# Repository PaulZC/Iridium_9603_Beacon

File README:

########################
# Iridium 9603N Beacon #
########################

A lightweight Iridium 9603N + GPS Beacon (Tracker)
Suitable for High Altitude Ballooning

*** Version 3 now includes u-blox SAM-M8Q GNSS and the option of solar power ***
You can find the latest (untested) files in:
https://github.com/PaulZC/Iridium_9603_Beacon/tree/master/V3
Details for the tested breadboard prototype can be found in:
https://github.com/PaulZC/Iridium_9603N_Solar_Beacon

The current stable release is Version 2:

See Iridium_9603_Beacon.pdf for a description of the project:
https://github.com/PaulZC/Iridium_9603_Beacon/blob/master/Iridium_9603_Beacon.pdf

See Iridium_9603_Beacon_V2.pdf for the PCB schematics, overlays and BOM:
https://github.com/PaulZC/Iridium_9603_Beacon/blob/master/Iridium_9603_Beacon_V2.pdf

The Arduino code can be found in Arduino\Iridium9603Beacon:
https://github.com/PaulZC/Iridium_9603_Beacon/tree/master/Arduino/Iridium9603Beacon

The Eagle files can be found in Eagle\V2:
https://github.com/PaulZC/Iridium_9603_Beacon/tree/master/Eagle/V2

This project is distributed under a Creative Commons Attribution + Share-alike (BY-SA) licence.
Please refer to section 5 of the licence for the Disclaimer of Warranties and Limitation of Liability.

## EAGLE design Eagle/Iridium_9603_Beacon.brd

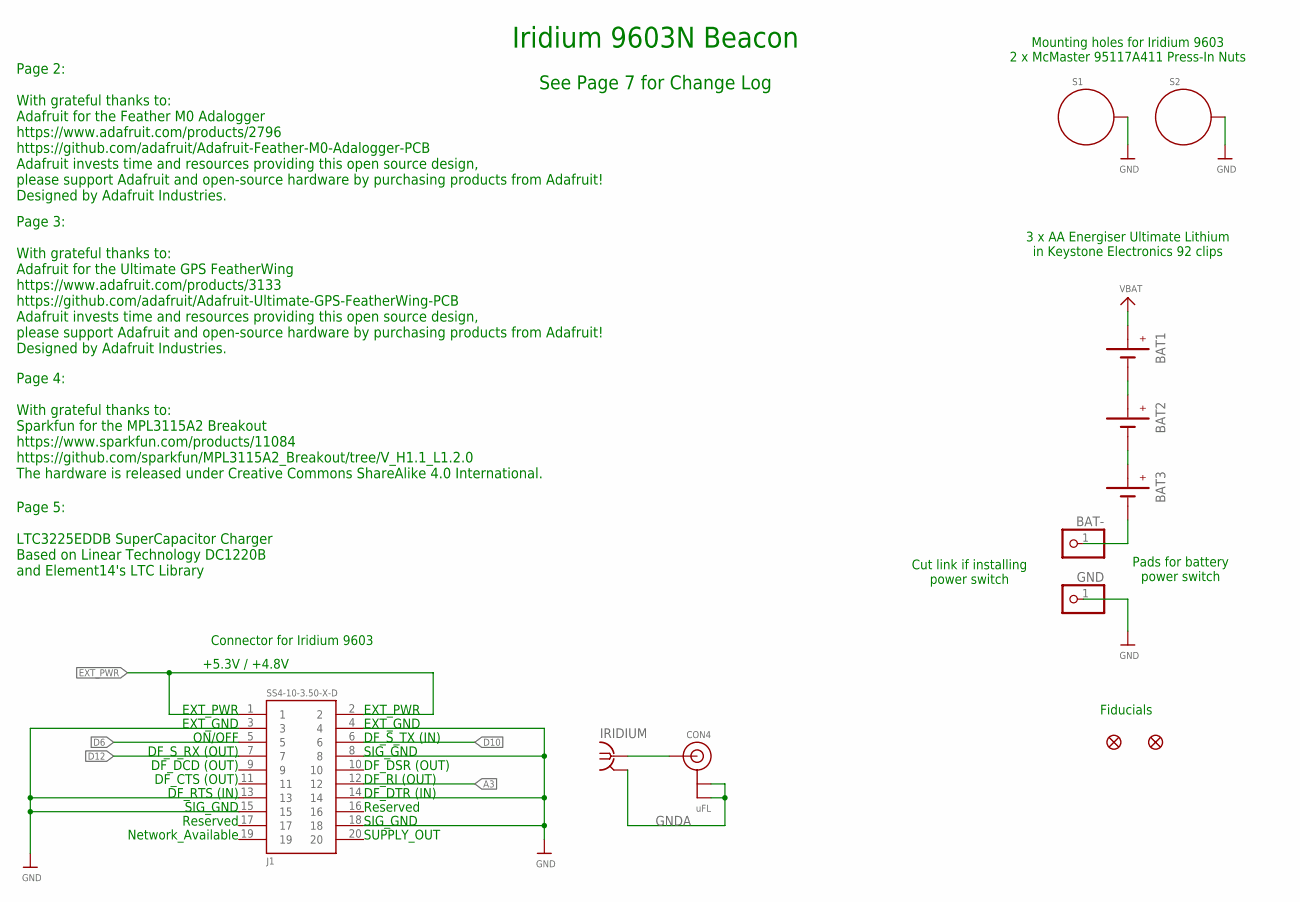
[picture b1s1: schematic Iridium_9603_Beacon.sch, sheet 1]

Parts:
BAT1, BAT2, BAT3: BATTERYKEYSTONE92; BATTERY-AAA-KEYSTONE92
BAT-: PINHD-1X1; 1X01
CON4: uFL; U.FL
FD1, FD2: FIDUCIAL1X2; FIDUCIAL-1X2
GND: PINHD-1X1; 1X01
IRIDIUM: SMA-142-0711-821/826; J502-ND-142-0711-821/826
J1: SS4-10-3.50-X-D
S1, S2: STANDOFF_ELECTRICALMCMASTER-95117A411; STANDOFF-ELECTRICAL-MCMASTER-95117A411

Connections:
A3: J1.12; also elsewhere on the board
D6: J1.5; also elsewhere on the board
D10: J1.6; also elsewhere on the board
D12: J1.7; also elsewhere on the board
EXT_PWR: J1.1, J1.2; also elsewhere on the board
GND: GND.1, J1.3, J1.4, J1.8, J1.13, J1.14, J1.15, J1.18, S1.P1, S2.P1; also elsewhere on the board
GNDA: CON4.1 (GND), CON4.2 (GND), IRIDIUM.G@1 (2), IRIDIUM.G@2 (2), IRIDIUM.G@3 (2), IRIDIUM.G@4 (2)
unnamed: CON4.3 (SIGNAL), IRIDIUM.1
unnamed: BAT1.GND@1 (-), BAT1.GND@2 (-), BAT2.PWR@1 (+), BAT2.PWR@2 (+)
unnamed: BAT3.GND@1 (-), BAT3.GND@2 (-), BAT-.1
unnamed: BAT2.GND@1 (-), BAT2.GND@2 (-), BAT3.PWR@1 (+), BAT3.PWR@2 (+)
VBAT: BAT1.PWR@1 (+), BAT1.PWR@2 (+); also elsewhere on the board

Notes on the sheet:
3 x AA Energiser Ultimate Lithium in Keystone Electronics 92 clips
Connector for Iridium 9603
Mounting holes for Iridium 9603 2 x McMaster 95117A411 Press-In Nuts
Iridium 9603N Beacon
Page 2: With grateful thanks to: Adafruit for the Feather M0 Adalogger https://www.adafruit.com/products/2796 https://github.com/adafruit/Adafruit-Feather-M0-Adalogger-PCB Adafruit invests time and resources providing this open source design, please support Adafruit and open-source hardware by purc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
Page 3: With grateful thanks to: Adafruit for the Ultimate GPS FeatherWing https://www.adafruit.com/products/3133 https://github.com/adafruit/Adafruit-Ultimate-GPS-FeatherWing-PCB Adafruit invests time and resources providing this open source design, please support Adafruit and open-source hardware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
Page 4: With grateful thanks to: Sparkfun for the MPL3115A2 Breakout https://www.sparkfun.com/products/11084 https://github.com/sparkfun/MPL3115A2_Breakout/tree/V_H1.1_L1.2.0 The hardware is released under Creative Commons ShareAlike 4.0 International.
EXT_PWR
EXT_GND
ON/OFF
DF_S_RX (OUT)
DF_DCD (OUT)
DF_CTS (OUT)
DF_RTS (IN)
SIG_GND
Reserved
Network_Available
DF_S_TX (IN)
DF_DSR (OUT)
DF_RI (OUT)
DF_DTR (IN)
SUPPLY_OUT
Page 5: LTC3225EDDB SuperCapacitor Charger Based on Linear Technology DC1220B and Element14's LTC Library
+5.3V / +4.8V
Fiducials
See Page 7 for Change Log
Pads for battery power switch
Cut link if installing power switch

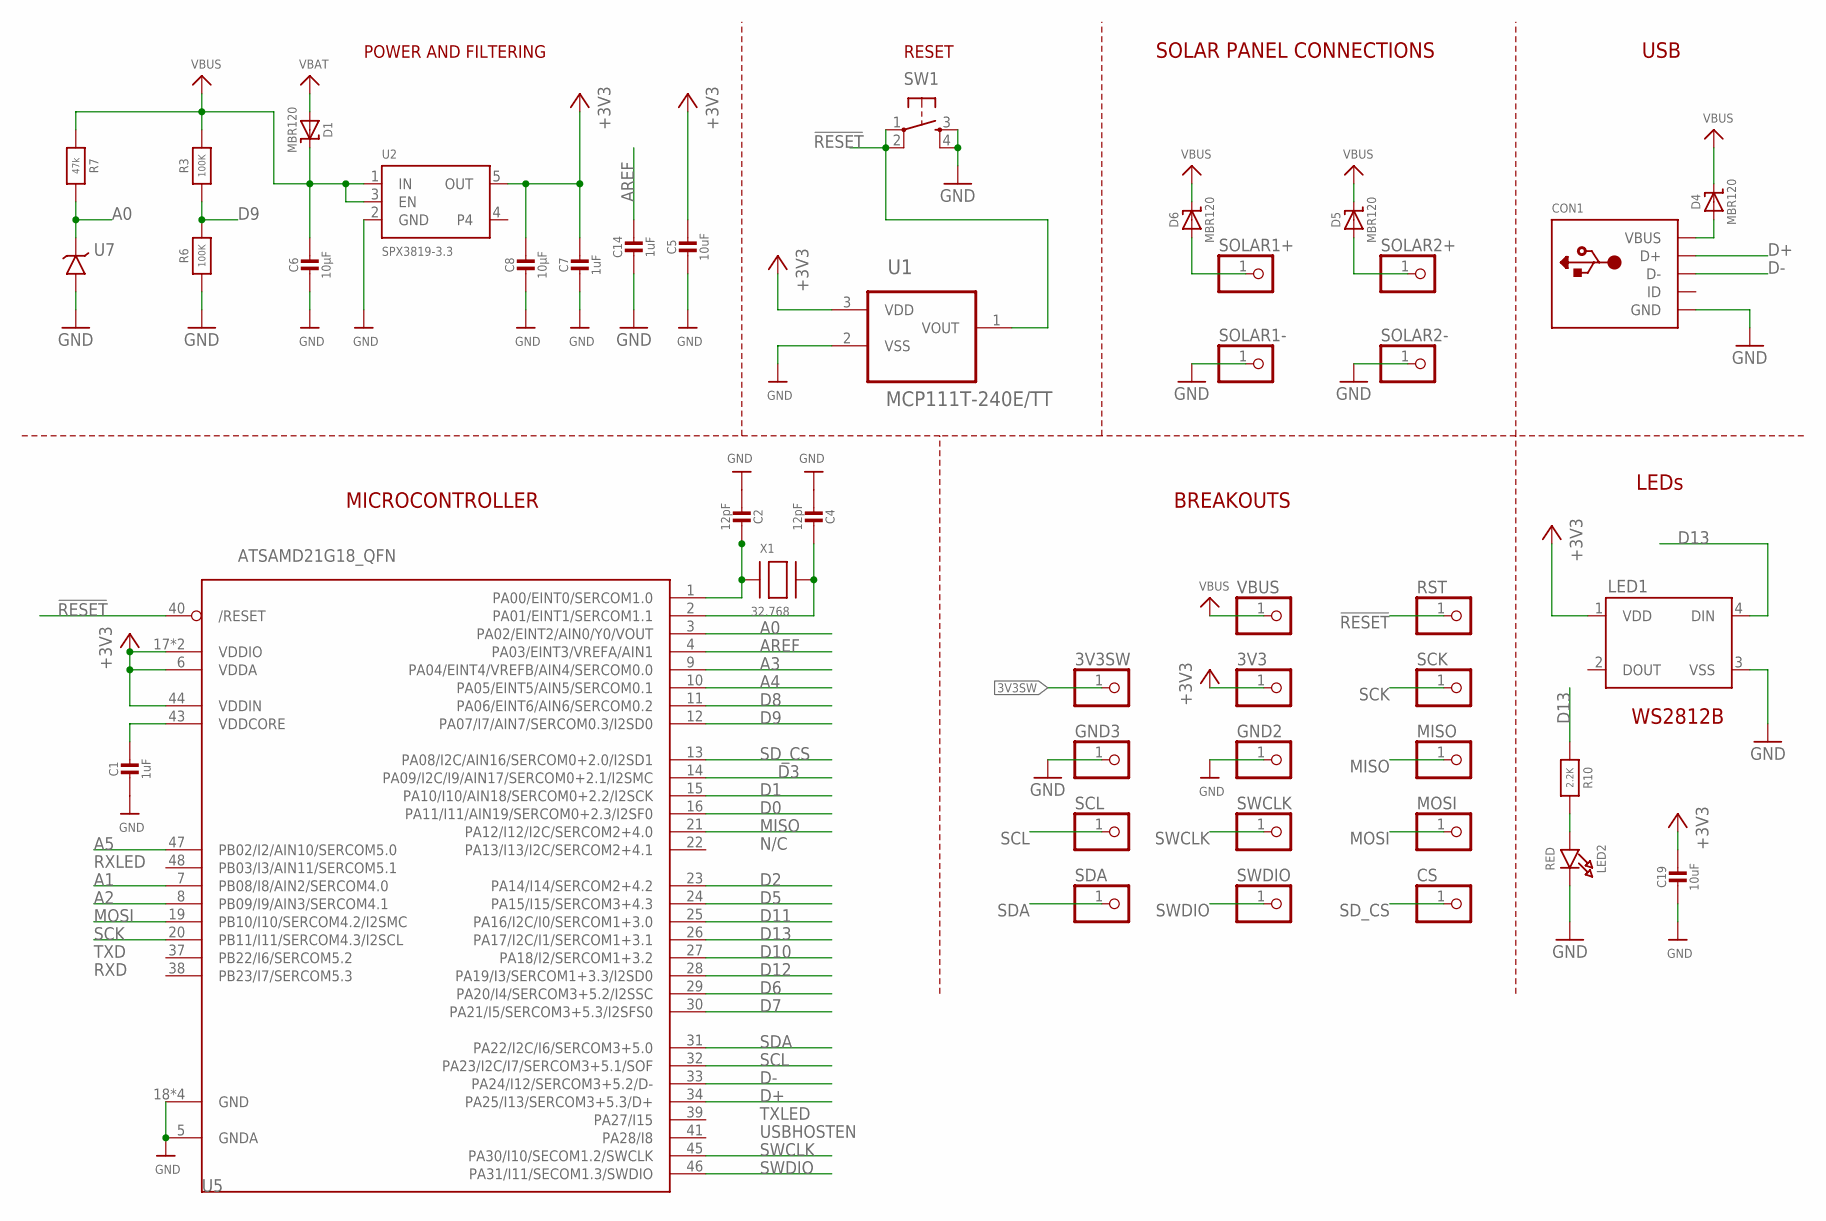
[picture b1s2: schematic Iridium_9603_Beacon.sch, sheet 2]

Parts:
3V3, 3V3SW: PINHD-1X1; 1X01
C1, C7, C14: 1uF; 0603-NO
C2, C4: 12pF; 0603-NO
C5, C19: 10uF; 0805-NO
C6, C8: 10µF; 0805-NO
CON1: MICROBUILDER_USBFCI_10103594_CORRECTED; MICROBUILDER_FCI_10103594_CORRECTED
CS: PINHD-1X1; 1X01
D1, D4, D5, D6: MBR120; SOD-123
GND2, GND3: PINHD-1X1; 1X01
LED1: WS2812B
LED2: RED; CHIPLED_0805_NOOUTLINE
MISO: PINHD-1X1; 1X01
MOSI: PINHD-1X1; 1X01
R3, R6: 100K; 0805-NO
R7: 47k; 0603-NO
R10: 2.2K; 0603-NO
RST: PINHD-1X1; 1X01
SCK: PINHD-1X1; 1X01
SCL: PINHD-1X1; 1X01
SDA: PINHD-1X1; 1X01
SOLAR1+, SOLAR1-, SOLAR2+, SOLAR2-: PINHD-1X1; 1X01
SW1: SWITCH_SPST_4_PINRECT; TACTILE_SWITCH_SMD_4.6X2.8MM
SWCLK: PINHD-1X1; 1X01
SWDIO: PINHD-1X1; 1X01
U1: MCP111T-240E/TT; SOT95P237X112-3N; MPN MCP111T-240E/TT
U2: SPX3819-3.3; SOT23-5
U5: ATSAMD21G18_QFN; TQFN48_7MM
U7: LT1634-1,25BMCMS8; MSOP8
VBUS: PINHD-1X1; 1X01
X1: 32.768; XTAL3215

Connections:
3V3SW: 3V3SW.1; also elsewhere on the board
!RESET: RST.1, SW1.1, SW1.2, U1.1 (VOUT), U5.40 (/RESET)
+3V3: 3V3.1, C5.1, C7.1, C8.1, C19.1, LED1.1 (VDD), U1.3 (VDD), U2.5 (OUT), U5.6 (VDDA), U5.17 (VDDIO), U5.36 (VDDIO), U5.44 (VDDIN); also elsewhere on the board
A0: R7.2, U5.3 (PA02/EINT2/AIN0/Y0/VOUT), U7.6 (VOUT)
A1: U5.7 (PB08/I8/AIN2/SERCOM4.0); also elsewhere on the board
A2: U5.8 (PB09/I9/AIN3/SERCOM4.1)
A3: U5.9 (PA04/EINT4/VREFB/AIN4/SERCOM0.0); also elsewhere on the board
A4: U5.10 (PA05/EINT5/AIN5/SERCOM0.1)
A5: U5.47 (PB02/I2/AIN10/SERCOM5.0); also elsewhere on the board
AREF: C14.1, U5.4 (PA03/EINT3/VREFA/AIN1)
D0: U5.16 (PA11/I11/AIN19/SERCOM0+2.3/I2SF0); also elsewhere on the board
D1: U5.15 (PA10/I10/AIN18/SERCOM0+2.2/I2SCK); also elsewhere on the board
D2: U5.23 (PA14/I14/SERCOM2+4.2); also elsewhere on the board
D3: U5.14 (PA09/I2C/I9/AIN17/SERCOM0+2.1/I2SMC)
D5: U5.24 (PA15/I15/SERCOM3+4.3); also elsewhere on the board
D6: U5.29 (PA20/I4/SERCOM3+5.2/I2SSC); also elsewhere on the board
D7: U5.30 (PA21/I5/SERCOM3+5.3/I2SFS0); also elsewhere on the board
D8: U5.11 (PA06/EINT6/AIN6/SERCOM0.2)
D9: R3.1, R6.2, U5.12 (PA07/I7/AIN7/SERCOM0.3/I2SD0)
D10: U5.27 (PA18/I2/SERCOM1+3.2); also elsewhere on the board
D11: U5.25 (PA16/I2C/I0/SERCOM1+3.0); also elsewhere on the board
D12: U5.28 (PA19/I3/SERCOM1+3.3/I2SD0); also elsewhere on the board
D13: LED1.4 (DIN), R10.1, U5.26 (PA17/I2C/I1/SERCOM1+3.1)
D+: CON1.D+, U5.34 (PA25/I13/SERCOM3+5.3/D+)
D-: CON1.D-, U5.33 (PA24/I12/SERCOM3+5.2/D-)
GND: C1.2, C2.2, C4.2, C5.2, C6.2, C7.2, C8.2, C14.2, C19.2, CON1.BASE@1 (GND), CON1.BASE@2 (GND), CON1.GND, CON1.SPRT@1 (GND), CON1.SPRT@2 (GND), CON1.SPRT@3 (GND), CON1.SPRT@4 (GND), GND2.1, GND3.1, LED1.3 (VSS), LED2.C, R6.1, SOLAR1-.1, SOLAR2-.1, SW1.3, SW1.4, U1.2 (VSS), U2.2 (GND), U5.5 (GNDA), U5.18 (GND), U5.35 (GND), U5.42 (GND), U5.THERMAL (GND), U7.4 (GND); also elsewhere on the board
MISO: MISO.1, U5.21 (PA12/I12/I2C/SERCOM2+4.0)
MOSI: MOSI.1, U5.19 (PB10/I10/SERCOM4.2/I2SMC)
unnamed: LED2.A, R10.2
unnamed: D6.A, SOLAR1+.1
unnamed: C2.1, U5.1 (PA00/EINT0/SERCOM1.0), X1.P$1
unnamed: C4.1, U5.2 (PA01/EINT1/SERCOM1.1), X1.P$2
unnamed: D5.A, SOLAR2+.1
unnamed: CON1.VBUS, D4.A
SCK: SCK.1, U5.20 (PB11/I11/SERCOM4.3/I2SCL)
SCL: SCL.1, U5.32 (PA23/I2C/I7/SERCOM3+5.1/SOF); also elsewhere on the board
SDA: SDA.1, U5.31 (PA22/I2C/I6/SERCOM3+5.0); also elsewhere on the board
SD_CS: CS.1, U5.13 (PA08/I2C/AIN16/SERCOM0+2.0/I2SD1)
SWCLK: SWCLK.1, U5.45 (PA30/I10/SECOM1.2/SWCLK)
SWDIO: SWDIO.1, U5.46 (PA31/I11/SECOM1.3/SWDIO)
VBAT: D1.A; also elsewhere on the board
VBUS: C6.1, D1.C, D4.C, D5.C, D6.C, R3.2, R7.1, U2.1 (IN), U2.3 (EN), VBUS.1; also elsewhere on the board
VDDCORE1: C1.1, U5.43 (VDDCORE)

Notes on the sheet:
POWER AND FILTERING
RESET
N/C
TXLED
USBHOSTEN
RXLED
TXD
RXD
USB
BREAKOUTS
LEDs
MICROCONTROLLER
WS2812B
SOLAR PANEL CONNECTIONS

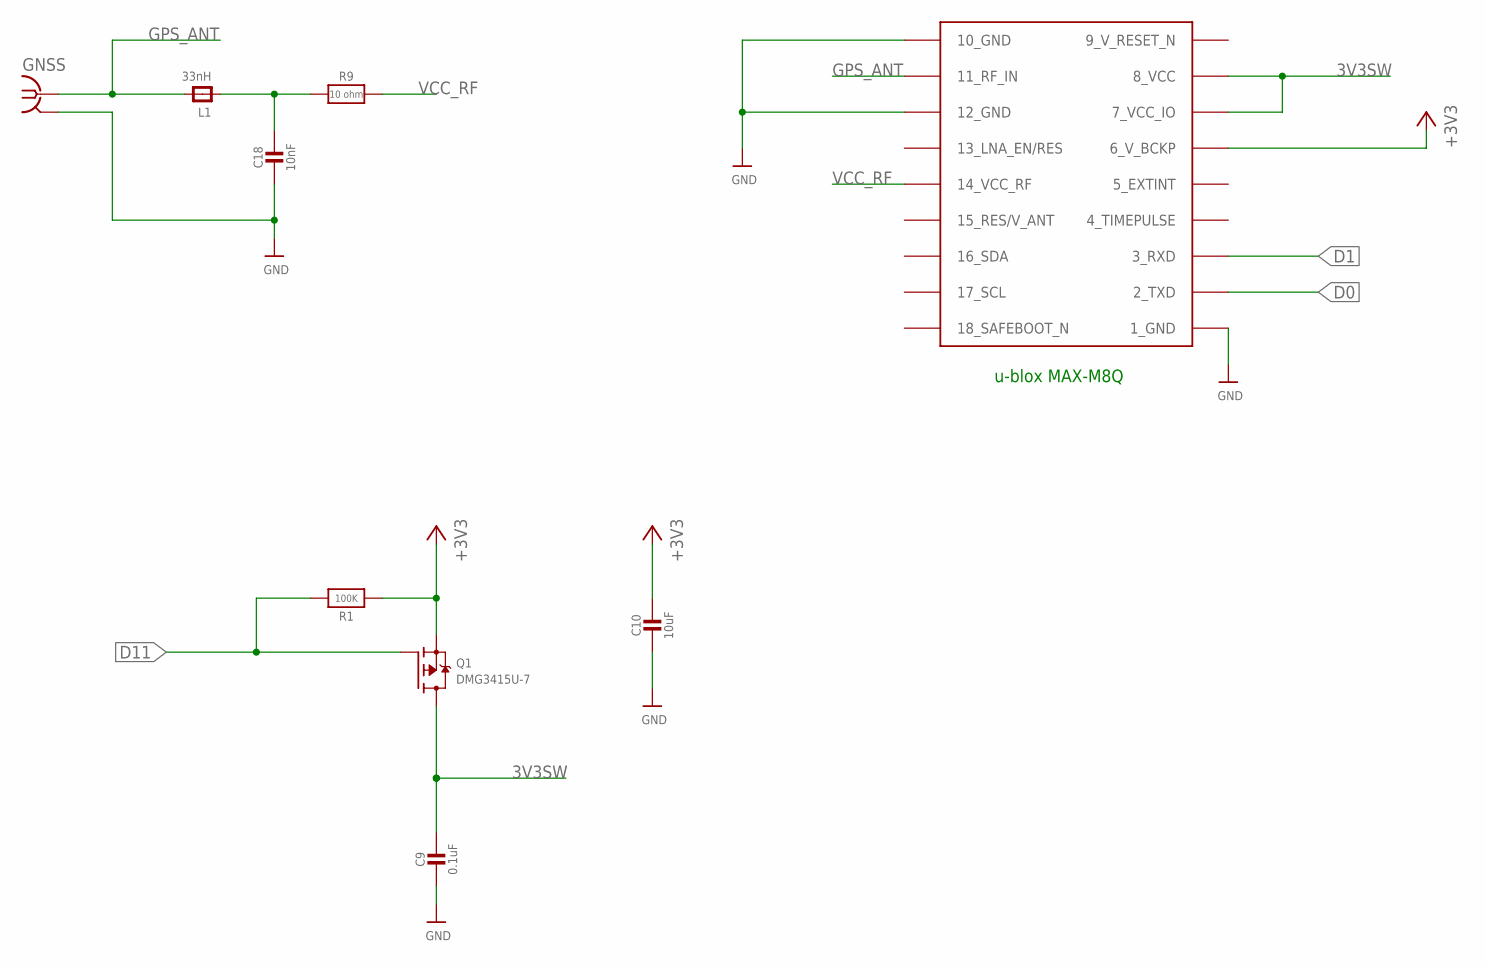
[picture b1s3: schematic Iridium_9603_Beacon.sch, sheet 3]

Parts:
C9: 0.1uF; 0805-NO
C10: 10uF; 0805-NO
C18: 10nF; 0805-NO
GNSS: SMA-142-0711-821/826; J502-ND-142-0711-821/826
L1: 33nH; 0805-NO
Q1: DMG3415U-7; SOT23-WIDE
R1: 100K; 0805-NO
R9: 10 ohm; 0805-NO
U6: MAX-M8

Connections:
3V3SW: C9.1, Q1.3 (D), U6.7_VCC_IO, U6.8_VCC; also elsewhere on the board
9_V_RESET_N: U6.9_RESET_N (9_V_RESET_N)
+3V3: C10.1, Q1.2 (S), R1.1, U6.6_V_BCKP; also elsewhere on the board
D0: U6.2_TXD; also elsewhere on the board
D1: U6.3_RXD; also elsewhere on the board
D11: Q1.1 (G), R1.2; also elsewhere on the board
GND: C9.2, C10.2, C18.2, GNSS.G@1 (2), GNSS.G@2 (2), GNSS.G@3 (2), GNSS.G@4 (2), U6.1_GND, U6.10_GND, U6.12_GND; also elsewhere on the board
GPS_ANT: GNSS.1, L1.2, U6.11_RF_IN
unnamed: C18.1, L1.1, R9.1
VCC_RF: R9.2, U6.14_VCC_RF

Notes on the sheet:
u-blox MAX-M8Q

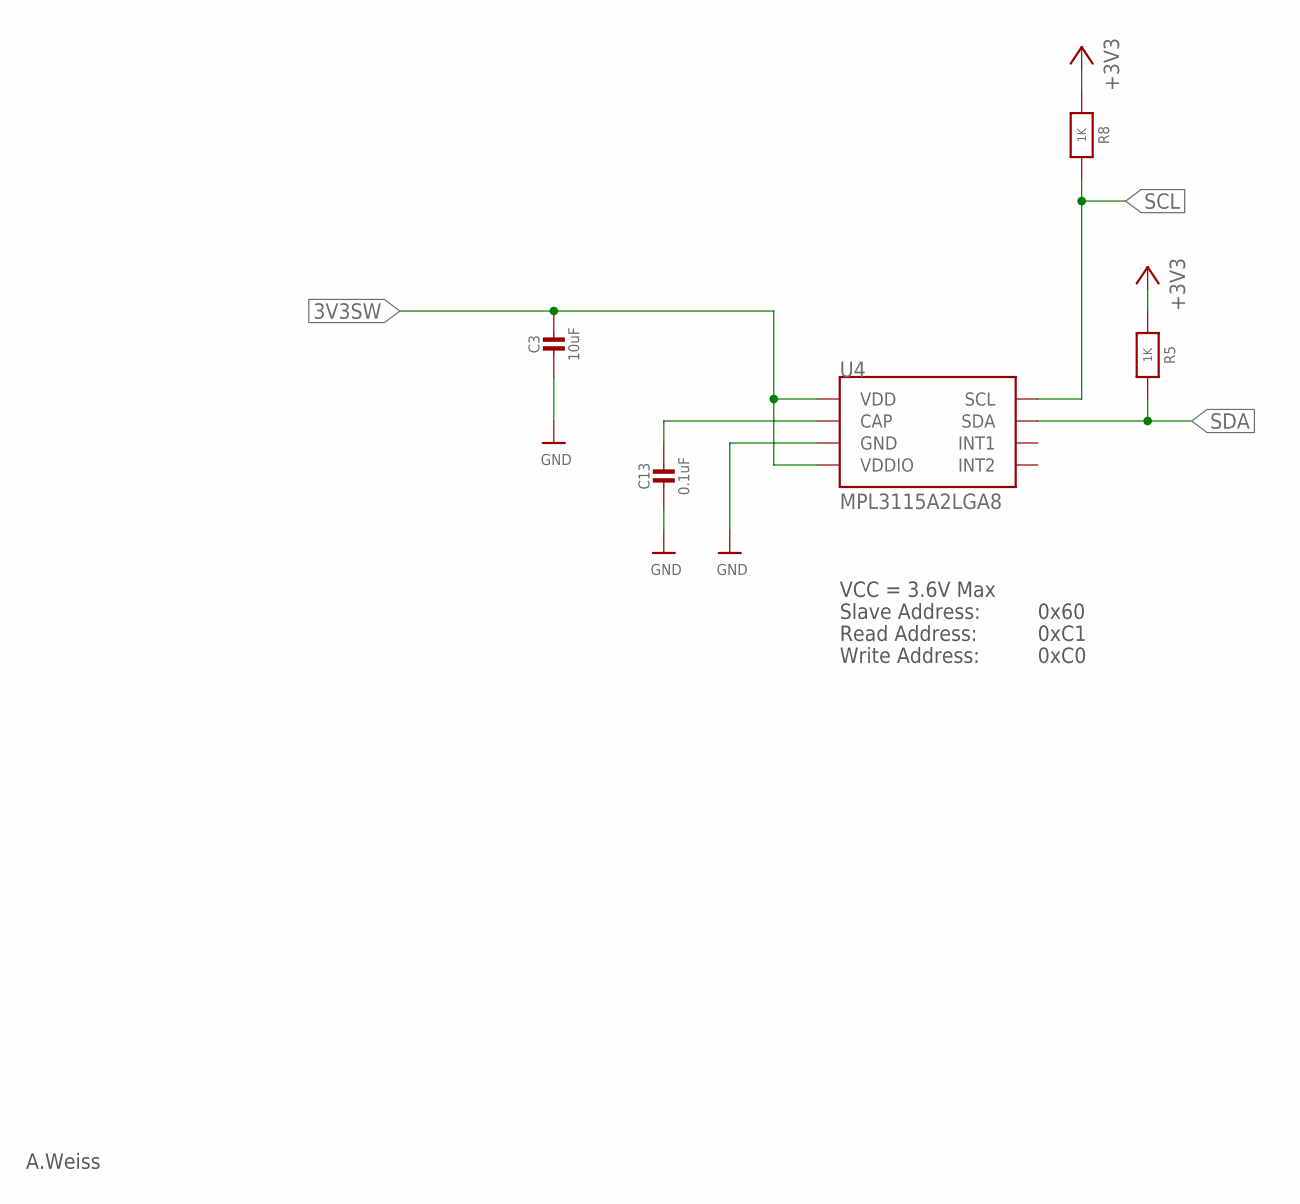
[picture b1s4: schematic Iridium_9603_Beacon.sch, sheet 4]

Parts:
C3: 10uF; 0805-NO
C13: 0.1uF; 0805-NO
R5, R8: 1K; 0603-NO
U4: MPL3115A2LGA8; LGA8

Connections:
3V3SW: C3.1, U4.1 (VDD), U4.4 (VDDIO); also elsewhere on the board
+3V3: R5.1, R8.1; also elsewhere on the board
GND: C3.2, C13.2, U4.3 (GND); also elsewhere on the board
unnamed: C13.1, U4.2 (CAP)
SCL: R8.2, U4.8 (SCL); also elsewhere on the board
SDA: R5.2, U4.7 (SDA); also elsewhere on the board

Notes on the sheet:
A.Weiss
VCC = 3.6V Max
Read Address:
Write Address:
Slave Address:
0x60
0xC1
0xC0

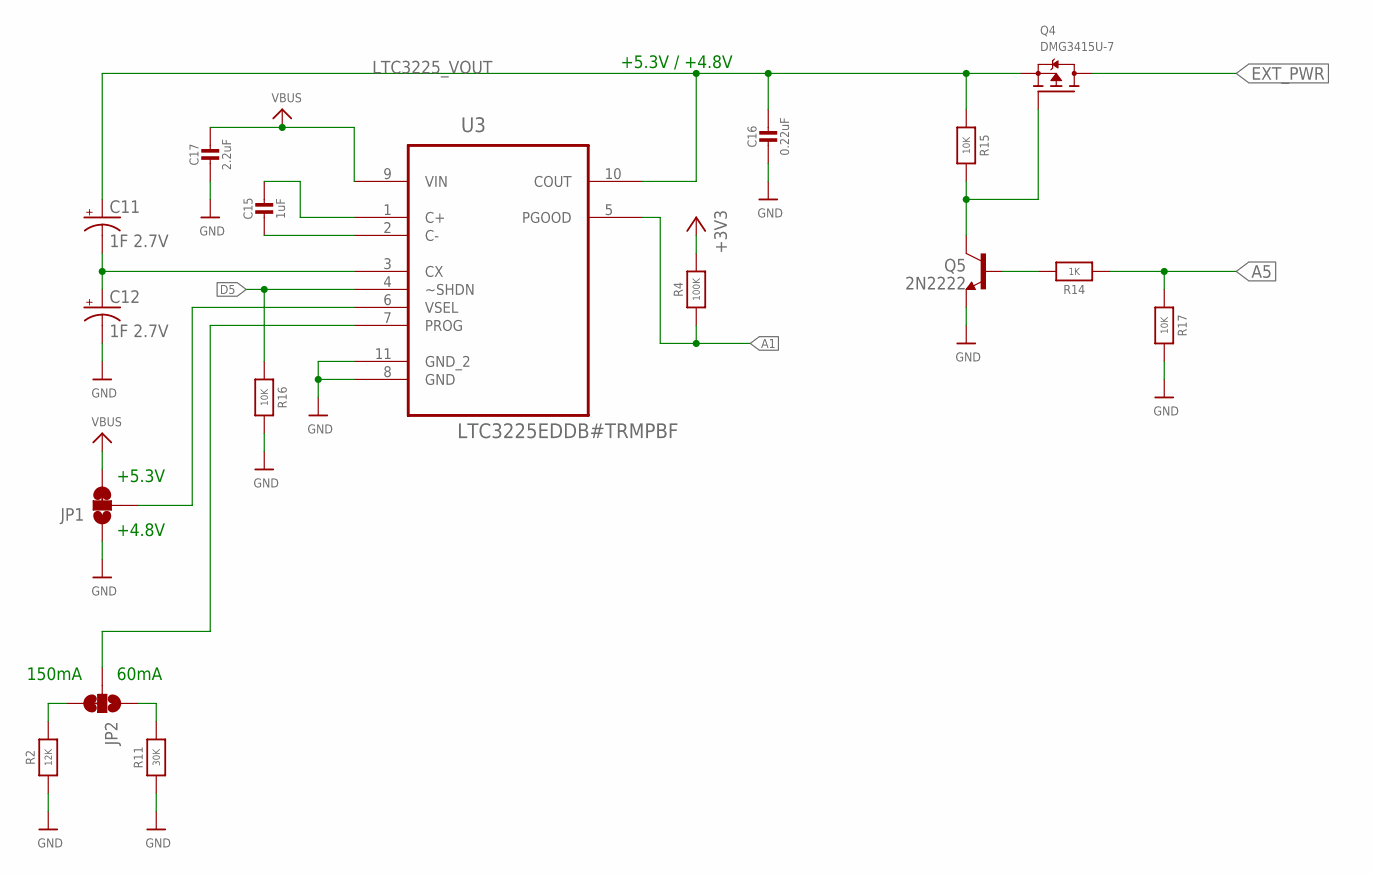
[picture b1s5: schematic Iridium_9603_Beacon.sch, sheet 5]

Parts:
C11, C12: 1F 2.7V; CPOL-RADIAL-1F-2.7V
C15: 1uF; 0603-NO
C16: 0.22uF; 0603-NO
C17: 2.2uF; 0805-NO
JP1, JP2: JUMPER-PAD-3-2OF3_NC_BY_TRACE_LARGE; PAD-JUMPER-3-2OF3_NC_BY_TRACE_YES_SILK_LARGE
Q4: DMG3415U-7; SOT23-WIDE
Q5: 2N2222; SOT23-BEC
R2: 12K; 0805-NO
R4: 100K; 0805-NO
R11: 30K; 0805-NO
R14: 1K; 0603-NO
R15, R16, R17: 10K; 0603-NO
U3: LTC3225EDDB#TRMPBF; DFN300X200-10L

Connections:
+3V3: R4.2; also elsewhere on the board
A1: R4.1, U3.5 (PGOOD); also elsewhere on the board
A5: R14.1, R17.1; also elsewhere on the board
D5: R16.1, U3.4 (~SHDN); also elsewhere on the board
EXT_PWR: Q4.3 (D); also elsewhere on the board
GND: C12.-, C16.2, C17.2, JP1.1, Q5.E, R2.1, R11.1, R16.2, R17.2, U3.8 (GND), U3.11 (GND_2); also elsewhere on the board
LTC3225_VOUT: C11.+, C16.1, Q4.2 (S), R15.1, U3.10 (COUT)
unnamed: C11.-, C12.+, U3.3 (CX)
unnamed: C15.2, U3.2 (C-)
unnamed: C15.1, U3.1 (C+)
unnamed: JP2.2, U3.7 (PROG)
unnamed: JP1.2, U3.6 (VSEL)
unnamed: JP2.3, R2.2
unnamed: JP2.1, R11.2
unnamed: Q4.1 (G), Q5.C, R15.2
unnamed: Q5.B, R14.2
VBUS: C17.1, JP1.3, U3.9 (VIN); also elsewhere on the board

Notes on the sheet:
+5.3V / +4.8V
+5.3V
+4.8V
150mA
60mA

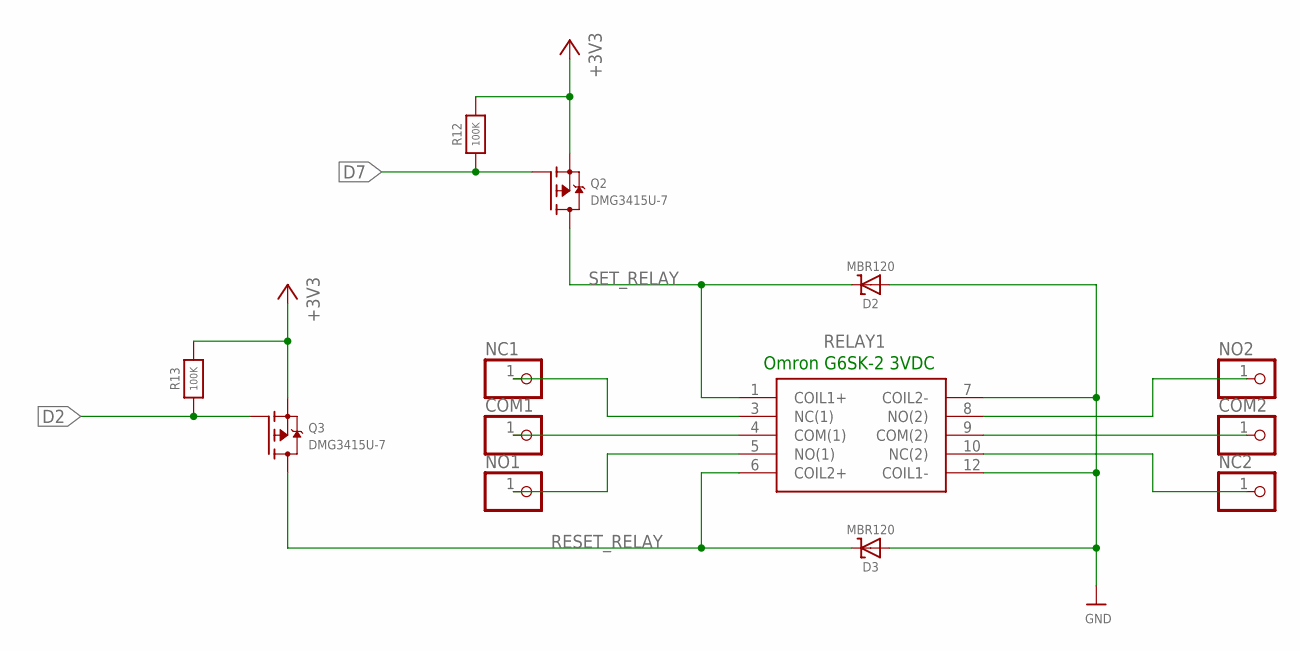
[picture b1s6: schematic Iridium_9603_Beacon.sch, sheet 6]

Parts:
COM1, COM2: PINHD-1X1; 1X01
D2, D3: MBR120; SOD-123
NC1, NC2: PINHD-1X1; 1X01
NO1, NO2: PINHD-1X1; 1X01
Q2, Q3: DMG3415U-7; SOT23-WIDE
R12, R13: 100K; 0805-NO
RELAY1: G6SK-2_DC5; G6SK2DC5

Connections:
+3V3: Q2.2 (S), Q3.2 (S), R12.2, R13.2; also elsewhere on the board
D2: Q3.1 (G), R13.1; also elsewhere on the board
D7: Q2.1 (G), R12.1; also elsewhere on the board
GND: D2.A, D3.A, RELAY1.7 (COIL2-), RELAY1.12 (COIL1-); also elsewhere on the board
unnamed: NC1.1, RELAY1.3 (NC(1))
unnamed: COM1.1, RELAY1.4 (COM(1))
unnamed: NO1.1, RELAY1.5 (NO(1))
unnamed: NO2.1, RELAY1.8 (NO(2))
unnamed: COM2.1, RELAY1.9 (COM(2))
unnamed: NC2.1, RELAY1.10 (NC(2))
RESET_RELAY: D3.C, Q3.3 (D), RELAY1.6 (COIL2+)
SET_RELAY: D2.C, Q2.3 (D), RELAY1.1 (COIL1+)

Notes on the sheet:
Omron G6SK-2 3VDC

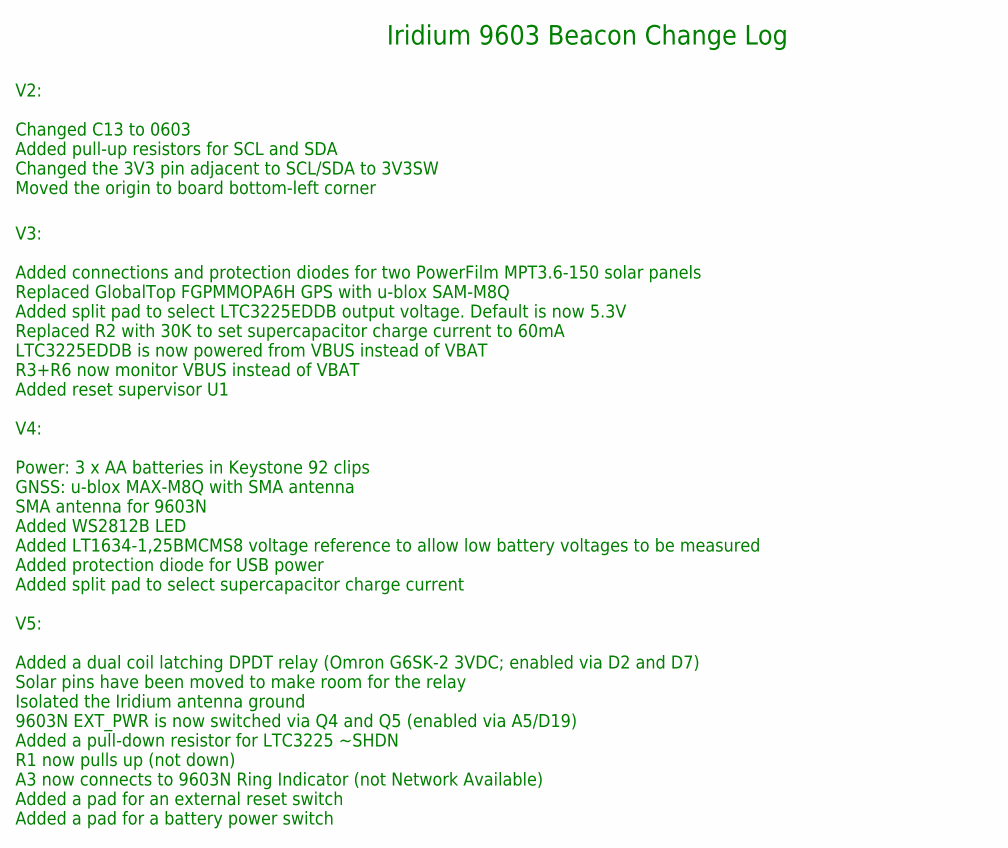
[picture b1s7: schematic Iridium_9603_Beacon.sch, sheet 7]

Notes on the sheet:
V2: Changed C13 to 0603 Added pull-up resistors for SCL and SDA Changed the 3V3 pin adjacent to SCL/SDA to 3V3SW Moved the origin to board bottom-left corner
Iridium 9603 Beacon Change Log
V3: Added connections and protection diodes for two PowerFilm MPT3.6-150 solar panels Replaced GlobalTop FGPMMOPA6H GPS with u-blox SAM-M8Q Added split pad to select LTC3225EDDB output voltage. Default is now 5.3V Replaced R2 with 30K to set supercapacitor charge current to 60mA LTC3225EDDB is now 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
V4: Power: 3 x AA batteries in Keystone 92 clips GNSS: u-blox MAX-M8Q with SMA antenna SMA antenna for 9603N Added WS2812B LED Added LT1634-1,25BMCMS8 voltage reference to allow low battery voltages to be measured Added protection diode for USB power Added split pad to select supercapacitor charge 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
V5: Added a dual coil latching DPDT relay (Omron G6SK-2 3VDC; enabled via D2 and D7) Solar pins have been moved to make room for the relay Isolated the Iridium antenna ground 9603N EXT_PWR is now switched via Q4 and Q5 (enabled via A5/D19) Added a pull-down resistor for LTC3225 ~SHDN R1 now pulls u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

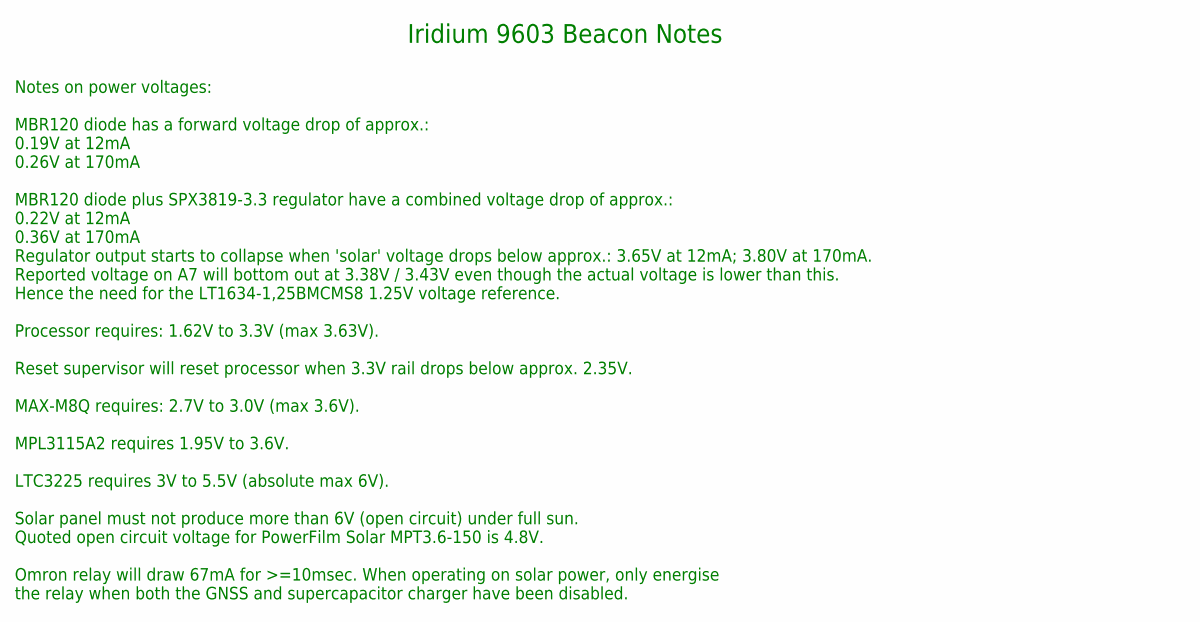
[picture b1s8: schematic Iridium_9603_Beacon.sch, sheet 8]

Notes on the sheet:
Iridium 9603 Beacon Notes
Notes on power voltages: MBR120 diode has a forward voltage drop of approx.: 0.19V at 12mA 0.26V at 170mA MBR120 diode plus SPX3819-3.3 regulator have a combined voltage drop of approx.: 0.22V at 12mA 0.36V at 170mA Regulator output starts to collapse when 'solar' voltage drops below approx.: 3.65V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

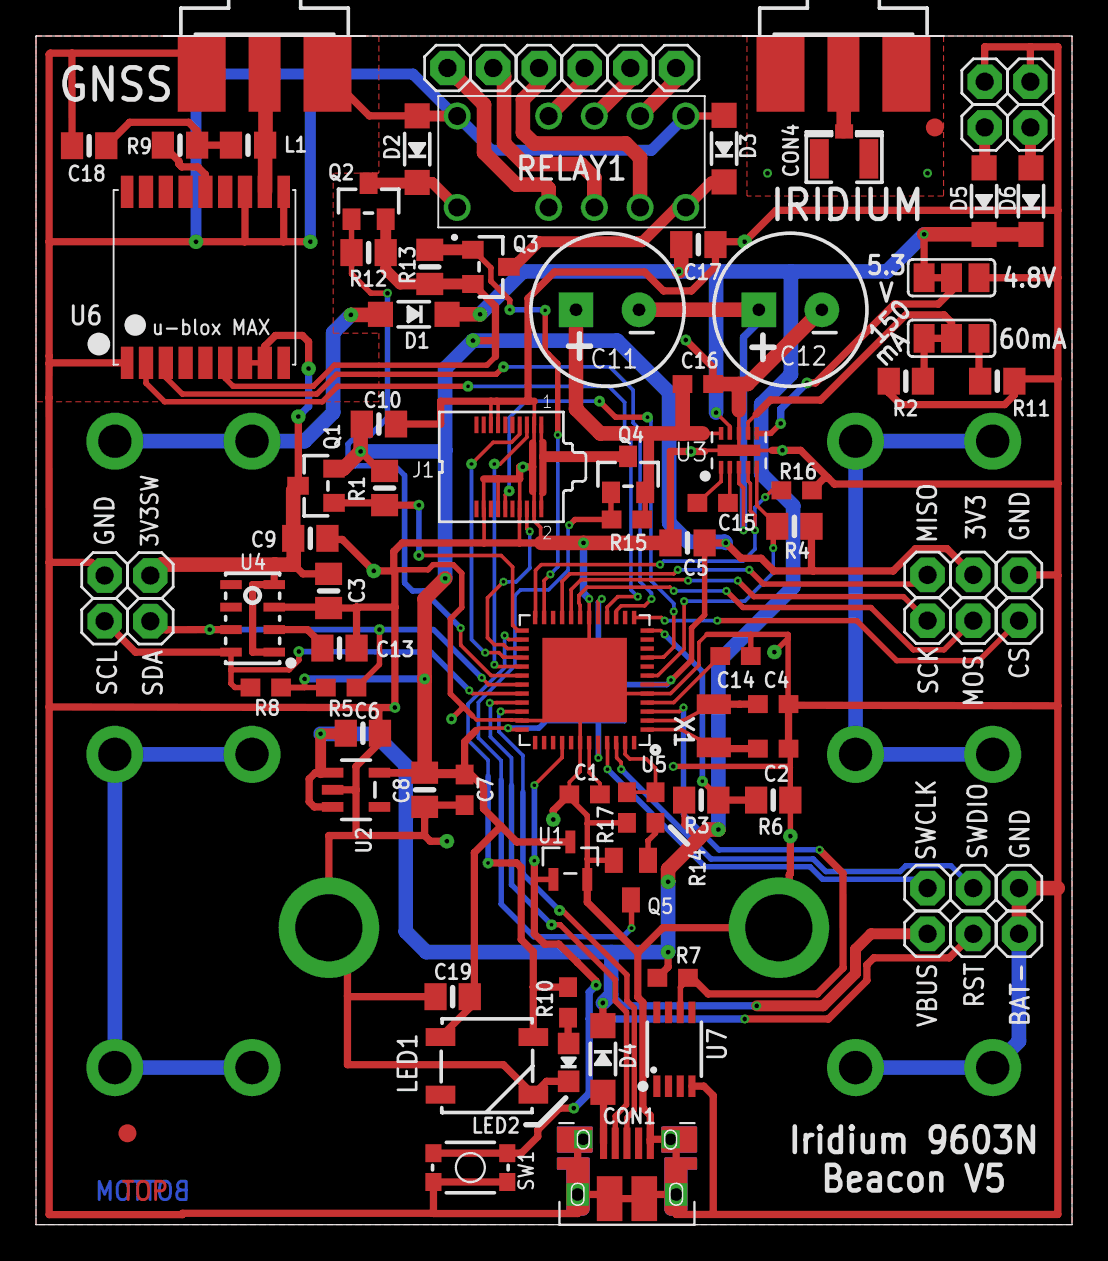
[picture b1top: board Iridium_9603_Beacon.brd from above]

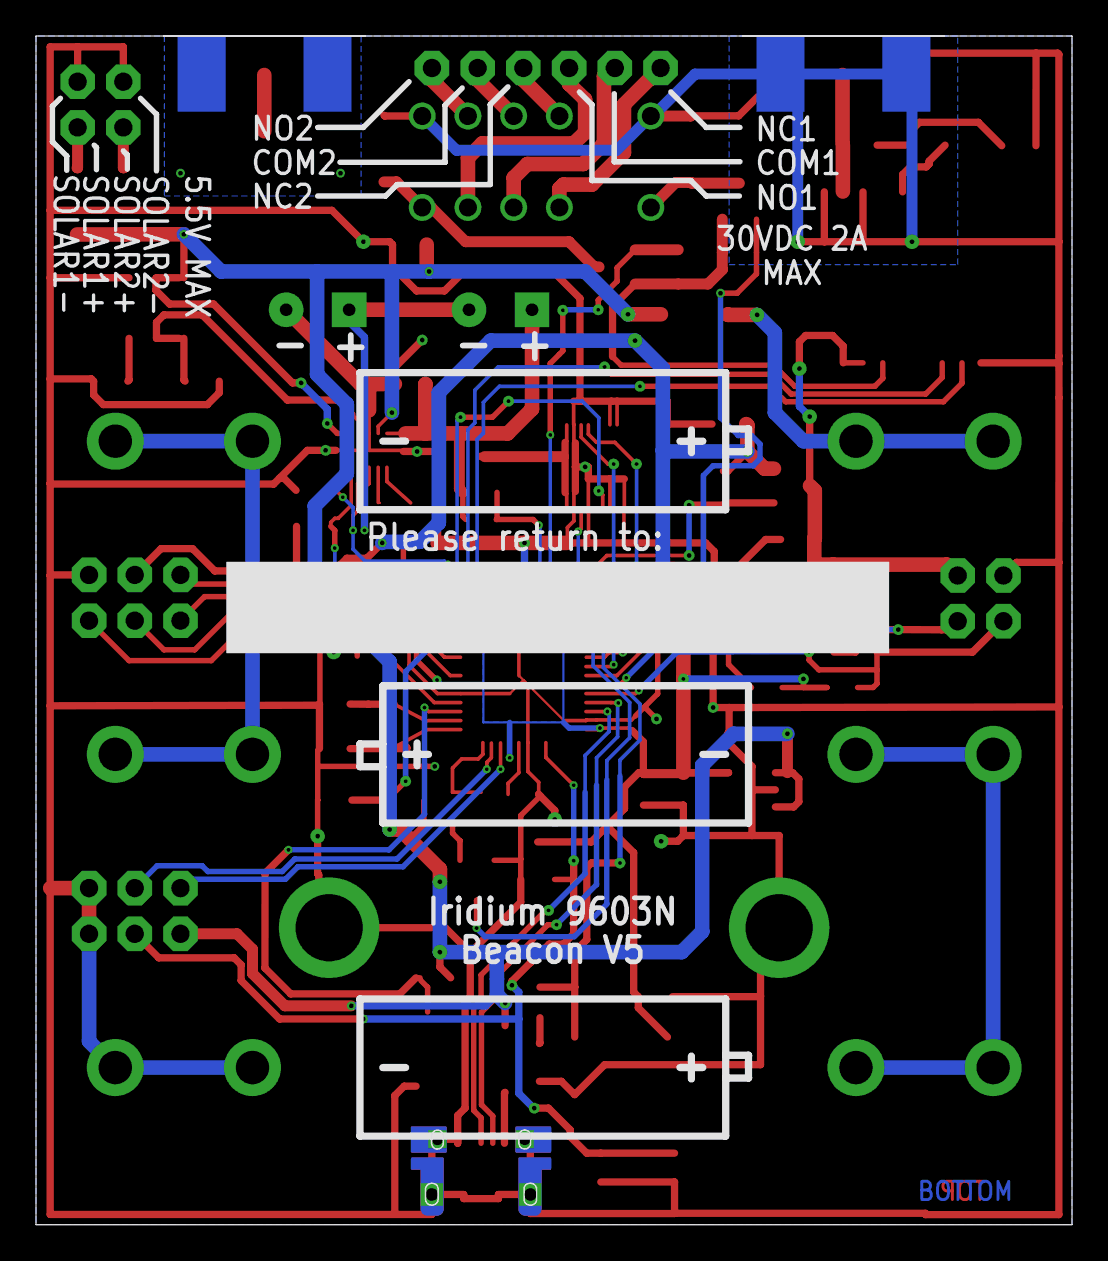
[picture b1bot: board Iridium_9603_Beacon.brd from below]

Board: 2 copper layers, 57.6 x 66.0 mm, 100 parts (3 on the bottom side), 67 nets.

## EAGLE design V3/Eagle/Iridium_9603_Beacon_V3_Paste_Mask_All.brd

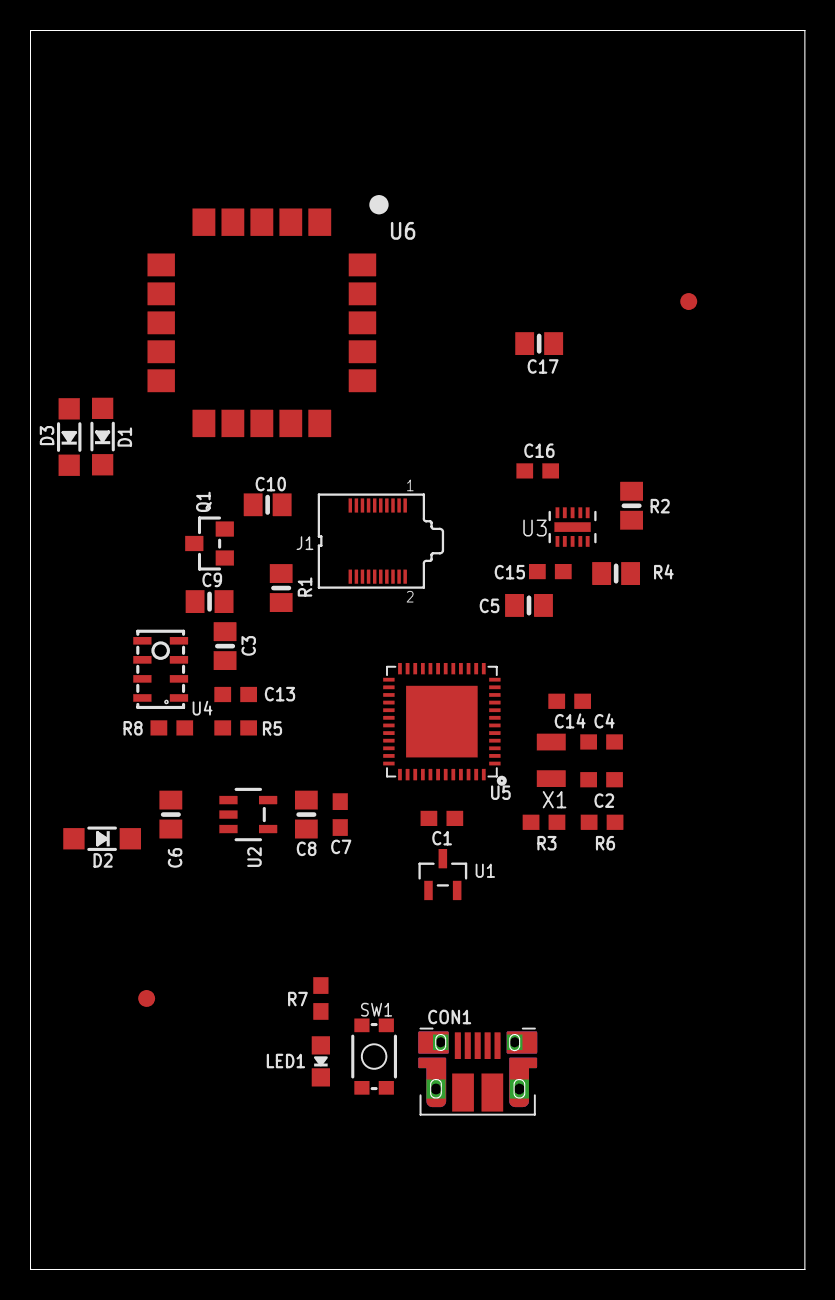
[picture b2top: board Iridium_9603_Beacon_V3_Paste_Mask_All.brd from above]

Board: 2 copper layers, 50.8 x 81.3 mm, 40 parts (0 on the bottom side), 2 nets, no tracks yet.

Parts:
C1, C7, C14, C15: 1uF; 0603-NO
C2, C4: 22pF; 0603-NO
C3, C5, C10: 10uF; 0805-NO
C6, C8: 10µF; 0805-NO
C9: 0.1uF; 0805-NO
C13: 0.1uF; 0603-NO
C16: 0.22uF; 0603-NO
C17: 2.2uF; 0805-NO
CON1: FCI_10103594
D1, D2, D3: MBR120; SOD-123
FD3, FD4: FIDUCIAL; FIDUCIAL-1X2-111%
J1: SS4-10-3.50-X-D
LED1: RED; CHIPLED_0805_NOOUTLINE
Q1: DMG3415U-7; SOT23-WIDE
R1, R4: 100K; 0805-NO
R2: 30K; 0805-NO
R3: 100k; 0603-NO
R5, R8: 1K; 0603-NO
R6: 100K; 0603-NO
R7: 2.2K; 0603-NO
SW1: TACTILE_SWITCH_SMD_4.6X2.8MM
U1: MCP111T-195I/TT; SOT95P237X112-3N
U2: SPX3819-3.3; SOT23-5
U3: LTC3225EDDB#TRMPBF; DFN300X200-10L
U4: MPL3115A2LGA8; LGA8
U5: ATSAMD21G18_QFN; TQFN48_7MM
U6: SAM-M8Q
X1: 32.768; XTAL3215

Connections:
GND: C16.2, CON1.BASE@1, CON1.BASE@2, CON1.GND, CON1.SPRT@1, CON1.SPRT@2, CON1.SPRT@3, CON1.SPRT@4, U2.2, U5.18, U5.35, U5.42, U5.THERMAL
VDDIO: U5.17, U5.36

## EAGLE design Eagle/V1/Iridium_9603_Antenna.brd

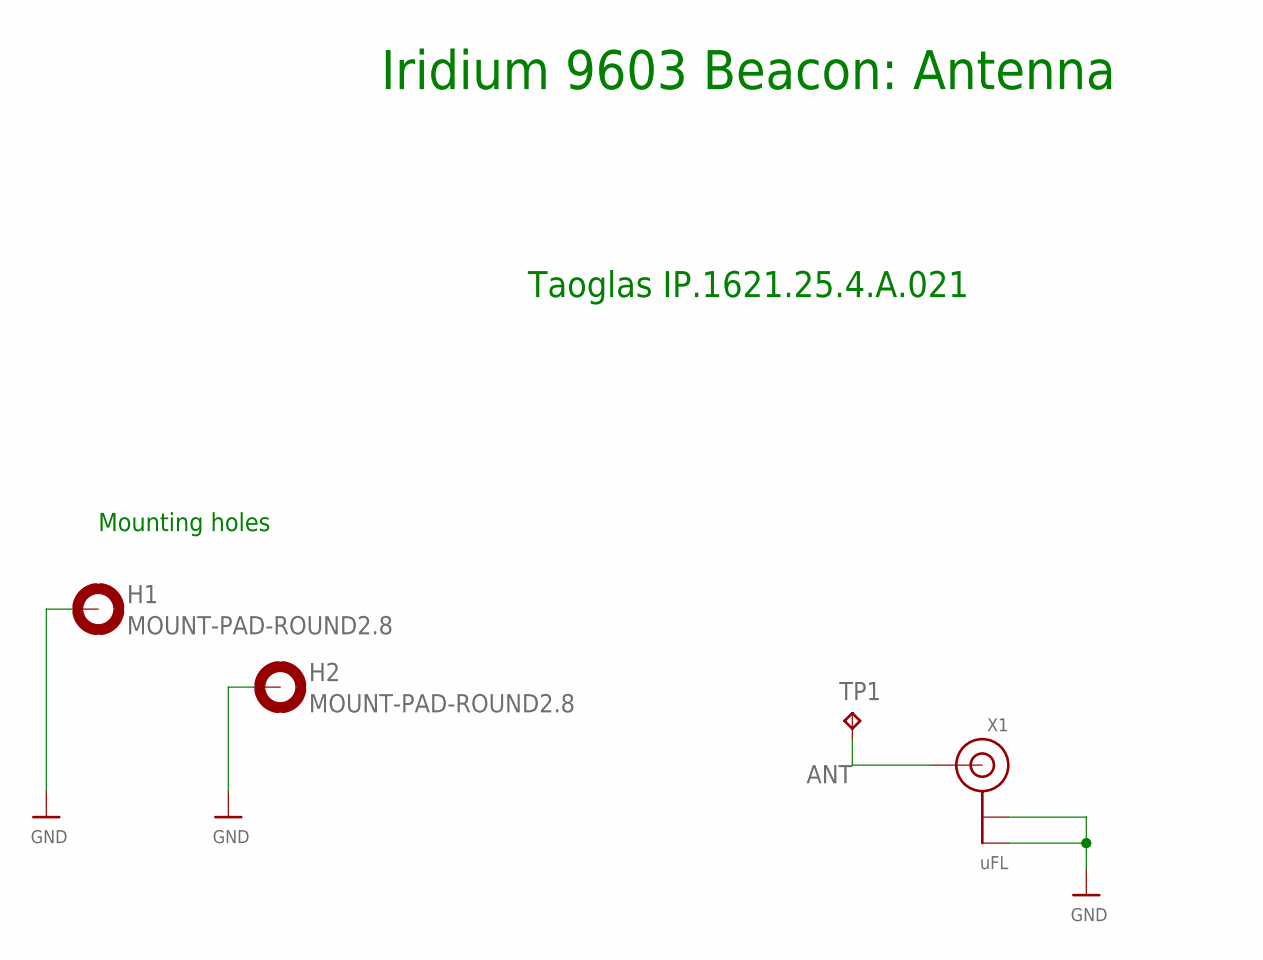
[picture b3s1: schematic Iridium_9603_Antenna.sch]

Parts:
H1, H2: MOUNT-PAD-ROUND2.8; 2,8-PAD
TP1: TPB2,54; B2,54
X1: uFL; U.FL

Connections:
ANT: TP1.TP, X1.3 (SIGNAL)
GND: H1.B2,8, H2.B2,8, X1.1 (GND), X1.2 (GND)

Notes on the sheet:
Mounting holes
Iridium 9603 Beacon: Antenna
Taoglas IP.1621.25.4.A.021

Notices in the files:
parts and their libraries:
microbuilder: This work is placed in the public domain, and may be freely used for commercial and non-commercial work with the following conditions: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
SparkFun-Sensors: Licensing: CC v3.0 Share-Alike You are welcome to use this library for commercial purposes.
